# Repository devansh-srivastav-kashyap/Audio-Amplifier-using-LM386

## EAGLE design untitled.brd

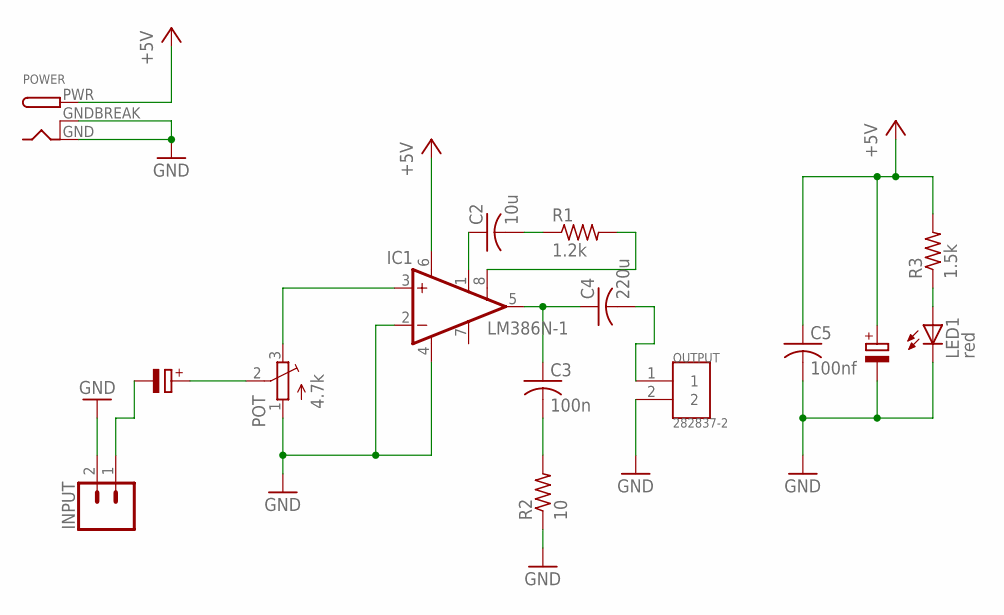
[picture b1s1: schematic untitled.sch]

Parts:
C2: 10u; C025-040X050
C3: 100n; C025-040X050
C4: 220u; C025-040X050
C5: 100nf; C025-040X050
IC1: LM386N-1; DIL08
INPUT: CONN_02; 1X02
LED1: red; LED3MM
OUTPUT: 282837-2; TE_282837-2
POT: 4.7k; TRIM-3386
POWER: DCBARRELPTH; DCJACK_2MM_PTH
R1: 1.2k; 0204/5
R2: 10; 0204/5
R3: 1.5k; 0204/5

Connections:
+5V: C5.1, IC1.6 (VS), POWER.PWR, R3.2
GND: C5.2, IC1.2 (-IN), IC1.4 (GND), INPUT.2, LED1.K (C), OUTPUT.2, POT.1 (A), POWER.GND, POWER.GNDBREAK, R2.1
unnamed: C3.2, R2.2
unnamed: C4.2, OUTPUT.1
unnamed: C2.2, R1.1
unnamed: IC1.3 (+IN), POT.3 (E)
unnamed: IC1.8 (GAIN), R1.2
unnamed: C2.1, IC1.1 (GAIN)
unnamed: C3.1, C4.1, IC1.5 (OUT)
unnamed: LED1.A, R3.1

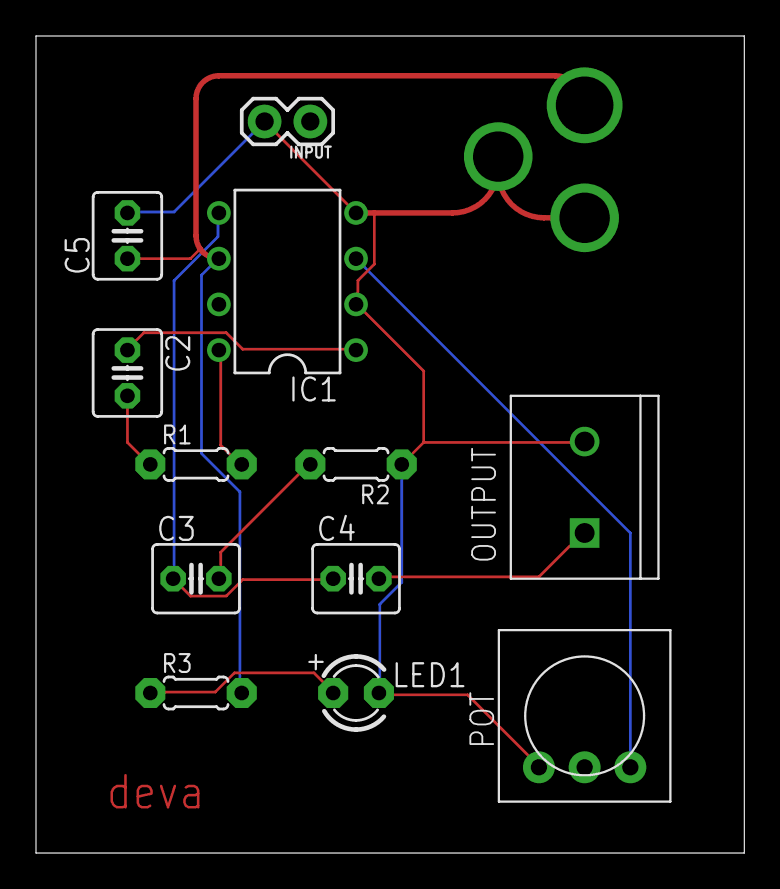
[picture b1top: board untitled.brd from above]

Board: 2 copper layers, 39.3 x 45.4 mm, 13 parts (1 on the bottom side), 10 nets.

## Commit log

2021-03-26 Gerber File

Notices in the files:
parts and their libraries:
SparkFun-Connectors: Licensing: Creative Commons ShareAlike 4.0 International - https://creativecommons.org/licenses/by-sa/4.0
